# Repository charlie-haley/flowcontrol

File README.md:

> **Due to not having to the time to work on this, this project will be archived. It may return in another form in the future.**
>
<p align="center" style="text-align: center">
   <a href="https://flowctl.app">
      <br/>
   </a>
   An open source, multiplatform fan controller.
</p>

**This project is still in a very early state. If you'd like to contribute, [please take a look at our outstanding issues](https://github.com/charlie-haley/flowcontrol/issues) and raise a PR** 
Alternatively, head over to [discussions](https://github.com/charlie-haley/flowcontrol/discussions) if you have any questions or ideas.

<p align="center" style="text-align: center">
   <br/>
</p>

## 📝 Getting Started

[Head over to the documentation to get started.](https://flowctl.app/getting-started/requirements/)

## ❓ FAQ

- **What is this?**<br/>
A fan controller with open-source hardware, software and a CLI.

- **Who's it for?**<br/>
It's primarily aimed at desktop computer users, but it can fit many use cases.

- **How can I use flowcontrol?**<br/>
At the moment, you will need the ability to solder so you can build the hardware, if it proves popular I may release some pre-built controllers. [You can find the documentation on building the controller here.](https://flowctl.app/getting-started/requirements/)

- **Why would I use this over X?**<br/>
This started out as a project for me to use personally, I was tired of expensive fan controllers with proprietary connectors and no Linux support.

## Special Thanks

Huge thank you to all the awesome open source projects that have made this possible!
- [Wails](https://github.com/wailsapp/wails)
- [Cobra](https://github.com/spf13/cobra)
- [Raspberry Pi Pico](https://www.raspberrypi.org/products/raspberry-pi-pico/)
- [YoungSerif](https://github.com/noirblancrouge/YoungSerif)
- [KiCad](https://www.kicad.org/)
- [Gridsome](https://github.com/gridsome/gridsome)

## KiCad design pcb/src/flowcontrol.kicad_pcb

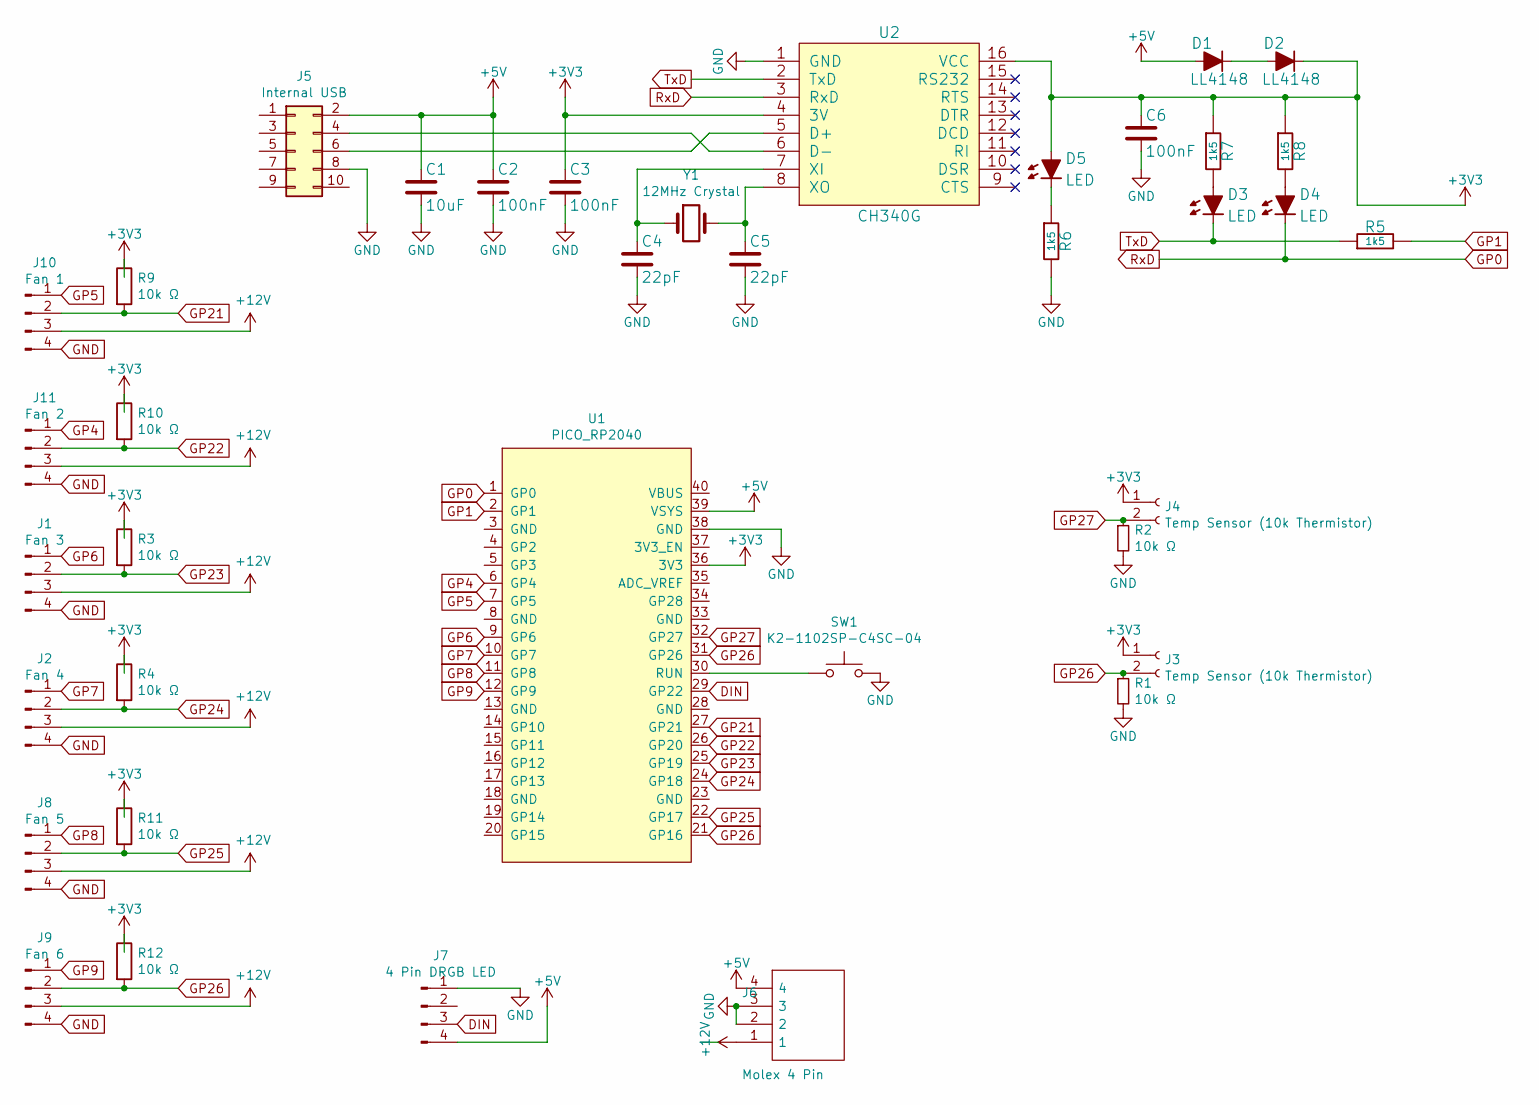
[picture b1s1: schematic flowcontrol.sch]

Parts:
C1: 10uF; C_0603_1608Metric
C2, C3, C6: 100nF; C_0603_1608Metric
C4, C5: 22pF; C_0603_1608Metric
D1, D2: LL4148; D_SMA
D3, D4, D5: LED; D_SMA
J1: Fan 3; PinHeader_1x04_P2.54mm_Horizontal
J2: Fan 4; PinHeader_1x04_P2.54mm_Horizontal
J3, J4: Temp Sensor (10k Thermistor); JST_XH_S2B-XH-A-1_1x02_P2.50mm_Horizontal
J5: Internal USB; PinSocket_2x05_P2.54mm_Horizontal
J6: Molex 4 Pin; 641737-1
J7: 4 Pin DRGB LED; PinHeader_1x04_P2.54mm_Horizontal
J8: Fan 5; PinHeader_1x04_P2.54mm_Horizontal
J9: Fan 6; PinHeader_1x04_P2.54mm_Horizontal
J10: Fan 1; PinHeader_1x04_P2.54mm_Horizontal
J11: Fan 2; PinHeader_1x04_P2.54mm_Horizontal
R1, R2, R3, R4, R9, R10, R11, R12: 10k Ω; R_0603_1608Metric
R5, R6, R7, R8: 1k5; R_0603_1608Metric
SW1: K2-1102SP-C4SC-04; SW_Push_1P1T_NO_6x6mm_H9.5mm
U1: PICO_RP2040; RPi_Pico_SMD_TH
U2: CH340G; SOIC-16_3.9x9.9mm_P1.27mm
Y1: 12MHz Crystal; Crystal_SMD_HC49-SD

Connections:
+3V3: C3.1, C6.1, D2.1 (A), D5.2 (C), J3.1, J4.1, R3.1, R4.1, R7.1, R8.1, R9.1, R10.1, R11.1, R12.1, U1.36 (3V3), U2.4 (3V), U2.16 (VCC)
+5V: C1.1, C2.1, D1.2 (C), J5.2, J6.4, J7.4, U1.39 (VSYS)
+12V: J1.3, J2.3, J6.1, J8.3, J9.3, J10.3, J11.3
DIN: J7.3, U1.29 (GP22)
GND: C1.2, C2.2, C3.2, C4.2, C5.2, C6.2, J1.4, J2.4, J5.8, J6.2, J6.3, J7.1, J8.4, J9.4, J10.4, J11.4, R1.2, R2.2, R6.2, SW1.2, U1.38 (GND), U2.1 (GND)
GP0: D4.1 (A), U1.1 (GP0), U2.3 (RxD)
GP1: R5.2, U1.2 (GP1)
GP4: J11.1, U1.6 (GP4)
GP5: J10.1, U1.7 (GP5)
GP6: J1.1, U1.9 (GP6)
GP7: J2.1, U1.10 (GP7)
GP8: J8.1, U1.11 (GP8)
GP9: J9.1, U1.12 (GP9)
GP21: J10.2, R9.2, U1.27 (GP21)
GP22: J11.2, R10.2, U1.26 (GP20)
GP23: J1.2, R3.2, U1.25 (GP19)
GP24: J2.2, R4.2, U1.24 (GP18)
GP25: J8.2, R11.2, U1.22 (GP17)
GP26: J3.2, J9.2, R1.1, R12.2, U1.21 (GP16), U1.31 (GP26)
GP27: J4.2, R2.1, U1.32 (GP27)
unnamed: C4.1, U2.7 (XI), Y1.1
unnamed: C5.1, U2.8 (XO), Y1.2
unnamed: D1.1 (A), D2.2 (C)
unnamed: D3.2 (C), R7.2
unnamed: D4.2 (C), R8.2
unnamed: D5.1 (A), R6.1
unnamed: J5.4, U2.6 (D-)
unnamed: J5.6, U2.5 (D+)
unnamed: SW1.1, U1.30 (RUN)
TxD: D3.1 (A), R5.1, U2.2 (TxD)

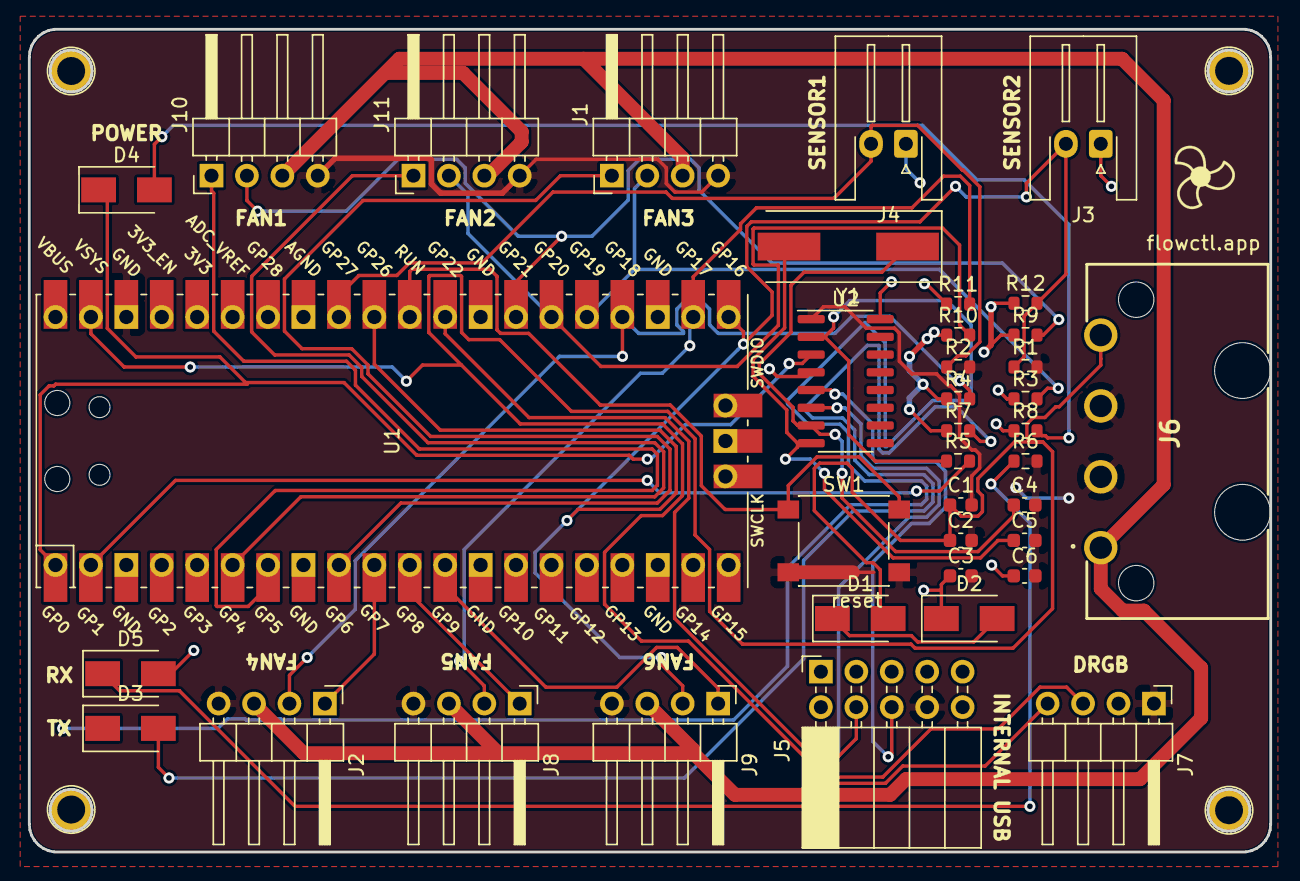
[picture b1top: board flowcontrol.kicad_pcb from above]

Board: 2 copper layers, 89.0 x 59.0 mm, 38 parts (0 on the bottom side), 30 nets.

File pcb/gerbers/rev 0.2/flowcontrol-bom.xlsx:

Comment | Designator | Footprint | LCSC Part #（optional）
10uF | C1 | C_0603_1608Metric
100nF | C2 | C_0603_1608Metric
100nF | C3 | C_0603_1608Metric
22pF | C4 | C_0603_1608Metric
22pF | C5 | C_0603_1608Metric
100nF | C6 | C_0603_1608Metric
LL4148 | D1 | D_SMA
LL4148 | D2 | D_SMA
LED | D3 | D_SMA
LED | D4 | D_SMA
LED | D5 | D_SMA
10k Ω | R1 | R_0603_1608Metric
10k Ω | R2 | R_0603_1608Metric
10k Ω | R3 | R_0603_1608Metric
10k Ω | R4 | R_0603_1608Metric
1k5 | R5 | R_0603_1608Metric
1k5 | R6 | R_0603_1608Metric
1k5 | R7 | R_0603_1608Metric
1k5 | R8 | R_0603_1608Metric
K2-1102SP-C4SC-04 | SW1 | SW_Push_1P1T_NO_6x6mm_H9.5mm
CH340G | U2 | SOIC-16_3.9x9.9mm_P1.27mm
12MHz Crystal | Y1 | Crystal_SMD_HC49-SD

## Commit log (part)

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2021-01-17 modify port num to prevent clash with logitech
2021-02-18 add missing files
2021-03-07 Add new firmware using rp2040
2021-03-09 Remove old firmware
2021-03-11 update PCB
2021-03-11 Revert "DNMY - Basic start to PCB/CLI updates (#11)"
    This reverts commit 4424d76fe94fc67d4e51bf4f38d9125f973b51b9.
2021-04-04 Migrate away from Chromely, use Wails instead
2021-04-05 add vue routers;tidy some fe components
2021-04-10 add basic LED colour changing support and config.json
2021-04-10 update dotnet version
2021-04-10 remove working dir
2021-04-10 install docker as part of workflow
2021-04-10 remove redundant import
2021-04-11 Local dev (#20)
    * update docs for local dev, add local container build
    * update local dev advice
2021-04-11 update release workflow
2021-04-11 add badge to readme
2021-04-19 Add sudo to debug
2021-04-22 Cleardown zip after build
2021-05-09 Bump hosted-git-info from 2.8.8 to 2.8.9 in /src/flowcontrol/frontend
    Bumps [hosted-git-info](https://github.com/npm/hosted-git-info) from 2.8.8 to 2.8.9.
    - [Release notes](https://github.com/npm/hosted-git-info/releases)
    - [Changelog](https://github.com/npm/hosted-git-info/blob/v2.8.9/CHANGELOG.md)
    - [Commits](https://github.com/npm/hosted-git-info/compare/v2.8.8...v2.8.9)
2021-05-09 add basic windows port detection
2021-05-09 add version number to settings page
2021-05-09 use ldflags to populate appver
2021-06-02 add v0.1 PCB files and gerbers
2021-06-02 add docs index
2021-06-02 Docs (#32)
    * add docs index
    * add docs index
2021-06-09 Add hugo Docs (#33)
    * add docs index
    * add docs index
    * add hugo docs
    * add hugo docs
2021-06-09 start new revision of PCB with integrated CH340G
2021-06-10 Bump ws from 6.2.1 to 6.2.2 in /src/flowcontrol/frontend (#35)
    Bumps [ws](https://github.com/websockets/ws) from 6.2.1 to 6.2.2.
    - [Release notes](https://github.com/websockets/ws/releases)
    - [Commits](https://github.com/websockets/ws/compare/6.2.1...6.2.2)
    ---
    updated-dependencies:
    - dependency-name: ws
2021-06-25 Bump postcss from 7.0.35 to 7.0.36 in /src/flowcontrol/frontend
    Bumps [postcss](https://github.com/postcss/postcss) from 7.0.35 to 7.0.36.
    - [Release notes](https://github.com/postcss/postcss/releases)
    - [Changelog](https://github.com/postcss/postcss/blob/main/CHANGELOG.md)
    - [Commits](https://github.com/postcss/postcss/compare/7.0.35...7.0.36)
    ---
    updated-dependencies:
2021-06-25 Create LICENSE
2021-06-26 v2 PCB + Website changes (#39)
    * add docs index
    * add docs index
    * add hugo docs
    * add hugo docs
    * update docs path
    * start new revision of PCB with integrated CH340G
2021-06-26 improvements to website landing page
2021-06-26 deploy: e975ad1aff3aa8a8f90f0f125301e6bd00c16584
2021-06-26 deploy: efe9119f2b0b4e1b335c9fc3c4f246964b3e6d50
2021-06-26 deploy: de573b092f1d3b982cea866b1b921ef3fa9adf35
2021-06-26 update logo and styling
2021-06-26 deploy: fded174ca0e13717f3e3d6b354df7f82c03edfc6
2021-06-26 deploy: 7cebcaf7e2f4c4a0fbf10a799bbabb0cf8cfdeb3
2021-06-27 deploy: 97dd7328a4bf6e1ac440fc4abfe9127c38fbaa94
2021-06-27 deploy: 948f5584f64f2b98c0e90d598bc897517f30c871
2021-06-27 deploy: 5c57adcb701a56bf636e9996a3f608181a95bc93
2021-06-27 fix favicon
2021-06-28 improve docs
2021-06-28 doc styling updates
2021-06-28 deploy: ed43723e4b256a920486104bfb3f2eb0d4925626
2021-06-28 update docs
2021-06-29 home page keeps breaking, nuclear option
2021-08-08 remove test firmwares
2021-08-10 docs styling, adding local dev instructions
2021-08-10 deploy: 1eb72e73fc4510bb549f6c1d20664e761d6e35e5
2021-08-12 Bump path-parse from 1.0.6 to 1.0.7 in /src/flowcontrol/frontend (#50)
    Bumps [path-parse](https://github.com/jbgutierrez/path-parse) from 1.0.6 to 1.0.7.
    - [Release notes](https://github.com/jbgutierrez/path-parse/releases)
    - [Commits](https://github.com/jbgutierrez/path-parse/commits/v1.0.7)
    ---
    updated-dependencies:
    - dependency-name: path-parse
2021-08-23 Styling updates to follow new branding
2021-08-23 Bump url-parse from 1.5.1 to 1.5.3 in /src/flowcontrol/frontend
    Bumps [url-parse](https://github.com/unshiftio/url-parse) from 1.5.1 to 1.5.3.
    - [Release notes](https://github.com/unshiftio/url-parse/releases)
    - [Commits](https://github.com/unshiftio/url-parse/compare/1.5.1...1.5.3)
    ---
    updated-dependencies:
    - dependency-name: url-parse
2021-09-02 Bump tar from 6.1.8 to 6.1.11 in /src/flowcontrol/frontend
    Bumps [tar](https://github.com/npm/node-tar) from 6.1.8 to 6.1.11.
    - [Release notes](https://github.com/npm/node-tar/releases)
    - [Changelog](https://github.com/npm/node-tar/blob/main/CHANGELOG.md)
    - [Commits](https://github.com/npm/node-tar/compare/v6.1.8...v6.1.11)
    ---
    updated-dependencies:
2021-09-12 start basic implementation of dark mode
2021-09-12 Remove wails pre-release update
    This is now redundant, remove pre-release update from pipeline.
2021-09-12 Update README.md (#60)
2021-09-12 Update ignore list for PR checks
2021-09-15 move settings items to components
2021-09-23 add annotation plugin
2021-10-27 test signing key
2021-10-28 add gerbers
2021-10-28 test status check
2021-11-20 fix: missing files
2021-11-20 docs: documentation rework (#73)
    * rename kicad files
    * test signing key
    * create revision 4 PCB
    * add silkscreen for components
    * add gerbers
    * docs: improve documentation/site
2021-11-20 fix: ensure doc release runs when CI change
2021-11-20 fix: publish dir
2021-11-20 docs: font references
2021-11-28 feat: wip implementation of tinygo firmware
2022-01-13 wip: rework to start using shared pkgs
2022-01-22 feat: implement tinygo (#75)
    * feat: implement tinygo
2022-01-24 feat: ci rework
2022-01-24 fix: use multiline yaml
2022-01-24 fix: use full file path
2022-01-24 fix: workflow structure
2022-01-25 fix: makefile path
2022-01-25 fix: add setup node to ci
2022-02-14 Bump ajv from 6.12.0 to 6.12.6 in /docs
    Bumps [ajv](https://github.com/ajv-validator/ajv) from 6.12.0 to 6.12.6.
    - [Release notes](https://github.com/ajv-validator/ajv/releases)
    - [Commits](https://github.com/ajv-validator/ajv/compare/v6.12.0...v6.12.6)
    ---
    updated-dependencies:
    - dependency-name: ajv
2022-02-19 Bump url-parse from 1.5.3 to 1.5.7 in /src/flowcontrol/cmd/gui/frontend
    Bumps [url-parse](https://github.com/unshiftio/url-parse) from 1.5.3 to 1.5.7.
    - [Release notes](https://github.com/unshiftio/url-parse/releases)
    - [Commits](https://github.com/unshiftio/url-parse/compare/1.5.3...1.5.7)
    ---
    updated-dependencies:
    - dependency-name: url-parse
2022-02-28 Bump url-parse from 1.5.3 to 1.5.10 in /src/flowcontrol/cmd/gui/frontend
    Bumps [url-parse](https://github.com/unshiftio/url-parse) from 1.5.3 to 1.5.10.
    - [Release notes](https://github.com/unshiftio/url-parse/releases)
    - [Commits](https://github.com/unshiftio/url-parse/compare/1.5.3...1.5.10)
    ---
    updated-dependencies:
    - dependency-name: url-parse
2022-04-29 Bump async from 2.6.3 to 2.6.4 in /docs
    Bumps [async](https://github.com/caolan/async) from 2.6.3 to 2.6.4.
    - [Release notes](https://github.com/caolan/async/releases)
    - [Changelog](https://github.com/caolan/async/blob/v2.6.4/CHANGELOG.md)
    - [Commits](https://github.com/caolan/async/compare/v2.6.3...v2.6.4)
    ---
    updated-dependencies:
2022-05-17 Bump lodash from 4.17.15 to 4.17.21 in /docs
    Bumps [lodash](https://github.com/lodash/lodash) from 4.17.15 to 4.17.21.
    - [Release notes](https://github.com/lodash/lodash/releases)
    - [Commits](https://github.com/lodash/lodash/compare/4.17.15...4.17.21)
    ---
    updated-dependencies:
    - dependency-name: lodash
2022-07-08 Bump moment from 2.24.0 to 2.29.4 in /docs
    Bumps [moment](https://github.com/moment/moment) from 2.24.0 to 2.29.4.
    - [Release notes](https://github.com/moment/moment/releases)
    - [Changelog](https://github.com/moment/moment/blob/develop/CHANGELOG.md)
    - [Commits](https://github.com/moment/moment/compare/2.24.0...2.29.4)
    ---
    updated-dependencies:
2022-11-12 Bump minimatch from 3.0.4 to 3.0.8 in /docs
    Bumps [minimatch](https://github.com/isaacs/minimatch) from 3.0.4 to 3.0.8.
    - [Release notes](https://github.com/isaacs/minimatch/releases)
    - [Commits](https://github.com/isaacs/minimatch/compare/v3.0.4...v3.0.8)
    ---
    updated-dependencies:
    - dependency-name: minimatch
2022-12-08 Bump decode-uri-component from 0.2.0 to 0.2.2 in /docs
    Bumps [decode-uri-component](https://github.com/SamVerschueren/decode-uri-component) from 0.2.0 to 0.2.2.
    - [Release notes](https://github.com/SamVerschueren/decode-uri-component/releases)
    - [Commits](https://github.com/SamVerschueren/decode-uri-component/compare/v0.2.0...v0.2.2)
    ---
    updated-dependencies:
    - dependency-name: decode-uri-component
2022-12-12 Bump qs from 6.5.2 to 6.5.3 in /src/flowcontrol/cmd/gui/frontend
    Bumps [qs](https://github.com/ljharb/qs) from 6.5.2 to 6.5.3.
    - [Release notes](https://github.com/ljharb/qs/releases)
    - [Changelog](https://github.com/ljharb/qs/blob/main/CHANGELOG.md)
    - [Commits](https://github.com/ljharb/qs/compare/v6.5.2...v6.5.3)
    ---
    updated-dependencies:
2022-12-14 Bump express from 4.17.1 to 4.18.2 in /src/flowcontrol/cmd/gui/frontend
    Bumps [express](https://github.com/expressjs/express) from 4.17.1 to 4.18.2.
    - [Release notes](https://github.com/expressjs/express/releases)
    - [Changelog](https://github.com/expressjs/express/blob/master/History.md)
    - [Commits](https://github.com/expressjs/express/compare/4.17.1...4.18.2)
    ---
    updated-dependencies:
2023-02-25 Bump golang.org/x/net in /src/flowcontrol
    Bumps [golang.org/x/net](https://github.com/golang/net) from 0.0.0-20210813160813-60bc85c4be6d to 0.7.0.
    - [Release notes](https://github.com/golang/net/releases)
    - [Commits](https://github.com/golang/net/commits/v0.7.0)
    ---
    updated-dependencies:
    - dependency-name: golang.org/x/net
